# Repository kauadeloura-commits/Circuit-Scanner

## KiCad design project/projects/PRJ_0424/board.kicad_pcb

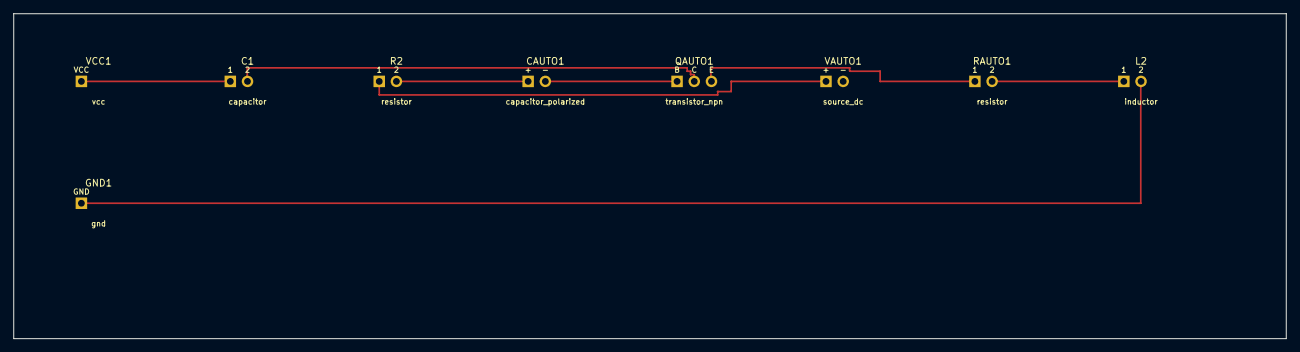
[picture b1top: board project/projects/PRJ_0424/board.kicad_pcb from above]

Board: 2 copper layers, 188.0 x 48.0 mm, 9 parts (0 on the bottom side), 8 nets.

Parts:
C1: capacitor; terminal_2
CAUTO1: capacitor_polarized; terminal_2
GND1: gnd; terminal_1
L2: inductor; terminal_2
QAUTO1: transistor_npn; terminal_3
R2: resistor; terminal_2
RAUTO1: resistor; terminal_2
VAUTO1: source_dc; terminal_2
VCC1: vcc; terminal_1

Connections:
GND: GND1.1, L2.2
NET_1: C1.1, VCC1.1
NET_2: C1.2, QAUTO1.2
NET_4: R2.1, VAUTO1.1
NET_5: CAUTO1.1, R2.2
NET_7: QAUTO1.3, RAUTO1.1
NET_9: L2.1, RAUTO1.2
NET_10: CAUTO1.2, QAUTO1.1

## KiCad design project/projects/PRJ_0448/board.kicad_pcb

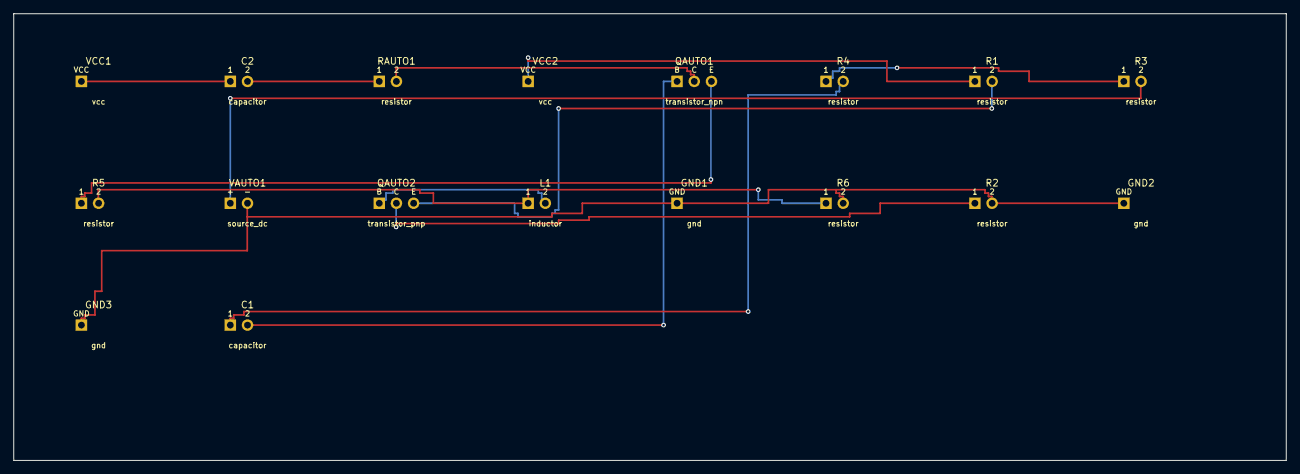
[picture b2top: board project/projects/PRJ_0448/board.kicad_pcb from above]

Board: 2 copper layers, 188.0 x 66.0 mm, 18 parts (0 on the bottom side), 14 nets.

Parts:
C1, C2: capacitor; terminal_2
GND1, GND2, GND3: gnd; terminal_1
L1: inductor; terminal_2
QAUTO1: transistor_npn; terminal_3
QAUTO2: transistor_pnp; terminal_3
R1, R2, R3, R4, R5, R6: resistor; terminal_2
RAUTO1: resistor; terminal_2
VAUTO1: source_dc; terminal_2
VCC1, VCC2: vcc; terminal_1

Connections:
GND: GND1.1, GND2.1, GND3.1, R2.2, R6.2, VAUTO1.2
NET_1: C2.1, VCC1.1
NET_2: C2.2, RAUTO1.1
NET_3: QAUTO1.2, RAUTO1.2
NET_4: R1.1, VCC2.1
NET_5: C1.2, QAUTO1.1
NET_6: QAUTO1.3, R5.1
NET_7: R3.1, R4.1
NET_8: C1.1, R4.2
NET_9: QAUTO2.3, R1.2
NET_10: R3.2, VAUTO1.1
NET_11: L1.1, R5.2, R6.1
NET_13: L1.2, QAUTO2.1
NET_14: QAUTO2.2, R2.1

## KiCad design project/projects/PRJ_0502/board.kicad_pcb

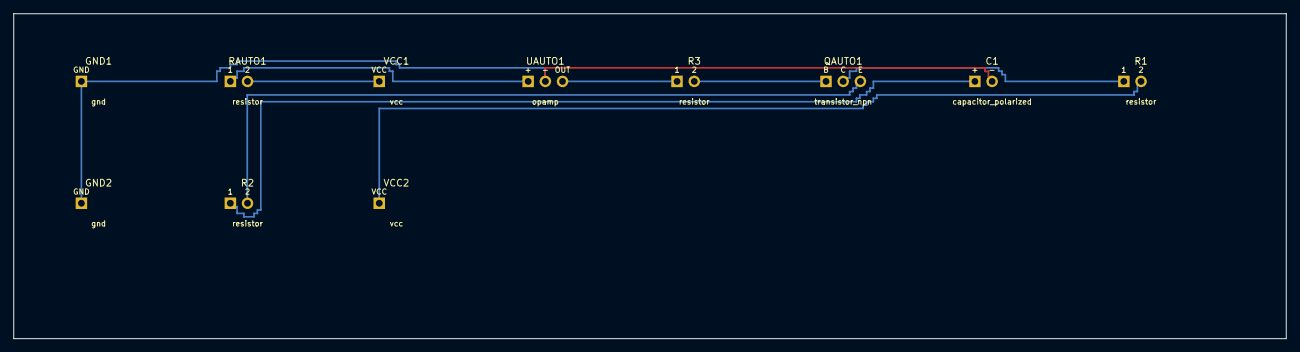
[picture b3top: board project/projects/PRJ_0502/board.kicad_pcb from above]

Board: 2 copper layers, 188.0 x 48.0 mm, 11 parts (0 on the bottom side), 9 nets.

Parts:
C1: capacitor_polarized; terminal_2
GND1, GND2: gnd; terminal_1
QAUTO1: transistor_npn; terminal_3
R1, R2, R3: resistor; terminal_2
RAUTO1: resistor; terminal_2
UAUTO1: opamp; terminal_3
VCC1, VCC2: vcc; terminal_1

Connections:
GND: C1.2, GND1.1, GND2.1, UAUTO1.2
NET_1: RAUTO1.1, UAUTO1.1
NET_2: R3.1, UAUTO1.3
NET_3: QAUTO1.1, R3.2
NET_4: QAUTO1.2, R1.1
NET_5: QAUTO1.3, R2.2
NET_6: C1.1, R2.1
NET_7: R1.2, VCC2.1
NET_8: RAUTO1.2, VCC1.1

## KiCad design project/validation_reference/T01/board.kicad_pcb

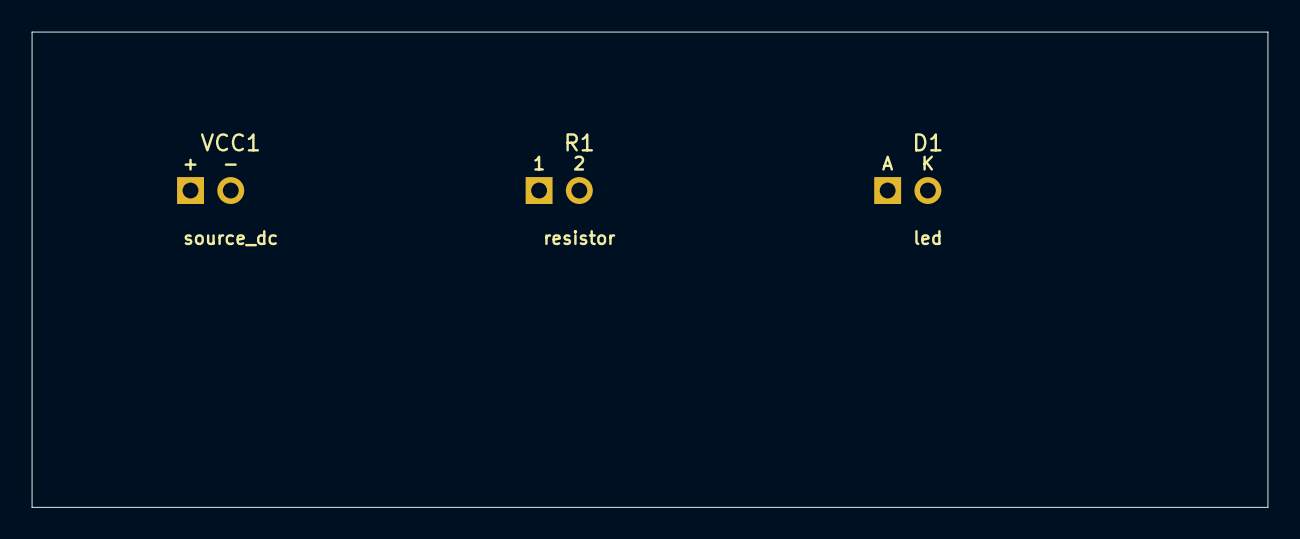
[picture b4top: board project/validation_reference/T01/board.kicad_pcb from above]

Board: 2 copper layers, 78.0 x 30.0 mm, 3 parts (0 on the bottom side), 3 nets, no tracks yet.

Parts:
D1: led; terminal_2
R1: resistor; terminal_2
VCC1: source_dc; terminal_2

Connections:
GND: D1.2, VCC1.2
VIN: R1.1, VCC1.1
VOUT: D1.1, R1.2

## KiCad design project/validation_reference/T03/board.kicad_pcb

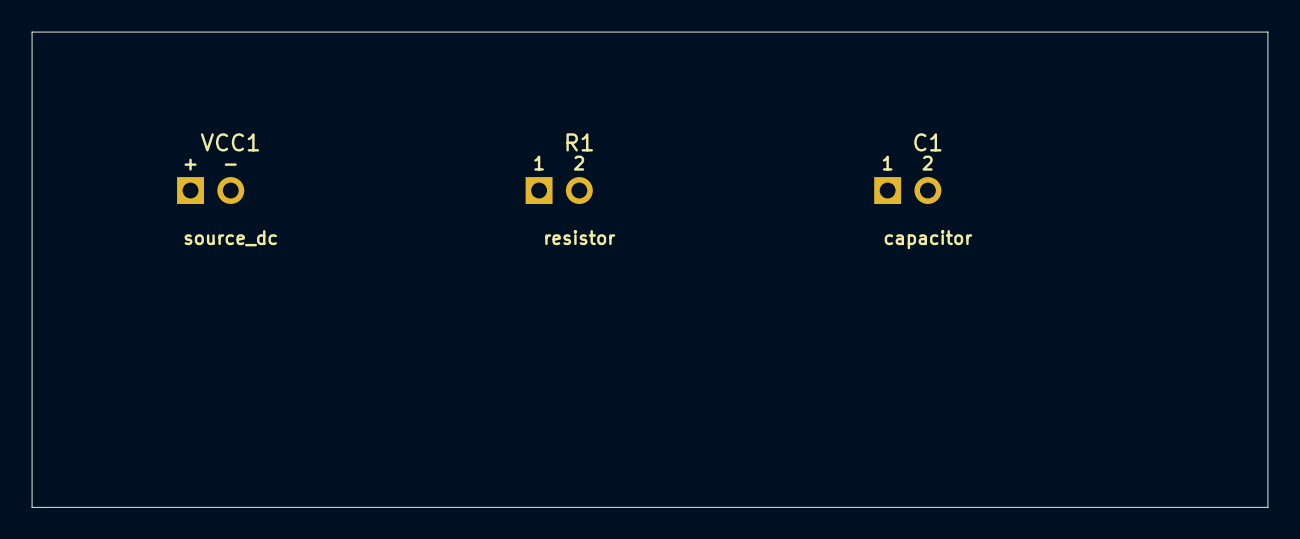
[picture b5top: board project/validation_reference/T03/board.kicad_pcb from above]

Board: 2 copper layers, 78.0 x 30.0 mm, 3 parts (0 on the bottom side), 3 nets, no tracks yet.

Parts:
C1: capacitor; terminal_2
R1: resistor; terminal_2
VCC1: source_dc; terminal_2

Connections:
GND: C1.2, VCC1.2
VIN: R1.1, VCC1.1
VOUT: C1.1, R1.2

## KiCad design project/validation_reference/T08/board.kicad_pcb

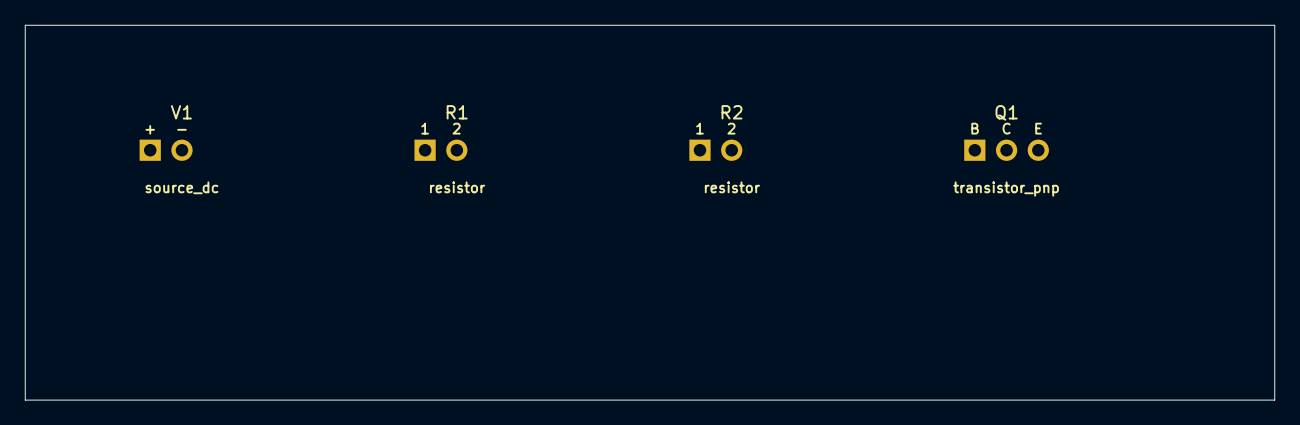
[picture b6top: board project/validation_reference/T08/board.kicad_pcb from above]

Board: 2 copper layers, 100.0 x 30.0 mm, 4 parts (0 on the bottom side), 4 nets, no tracks yet.

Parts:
Q1: transistor_pnp; terminal_3
R1, R2: resistor; terminal_2
V1: source_dc; terminal_2

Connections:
BASE: Q1.1, R1.2
GND: R1.1, R2.2, V1.2
OUT: Q1.2, R2.1
VIN: Q1.3, V1.1
